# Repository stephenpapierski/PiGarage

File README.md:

> [!IMPORTANT]
> This never worked well and there are much better solutions out there. I would recommend taking a look at [Konnected](https://konnected.io/collections/shop-now?filter.p.tag=Smart+Garage+Door+Openers) Garage Door Openers, which support Hubitat, Home Assistant, Control4 and other cloud based home automation platforms.
# PiGarage
This project contains the Raspberry Pi and Hubitat driver code for a Raspberry Pi hat for controlling a garage door through Hubitat. The hardware includes a relay for actuating the garage door controller, 2 door sensor inputs (open/closed), and status LEDs to communicate door status.

See the [project wiki](https://github.com/stephenpapierski/PiGarage/wiki) to get started.

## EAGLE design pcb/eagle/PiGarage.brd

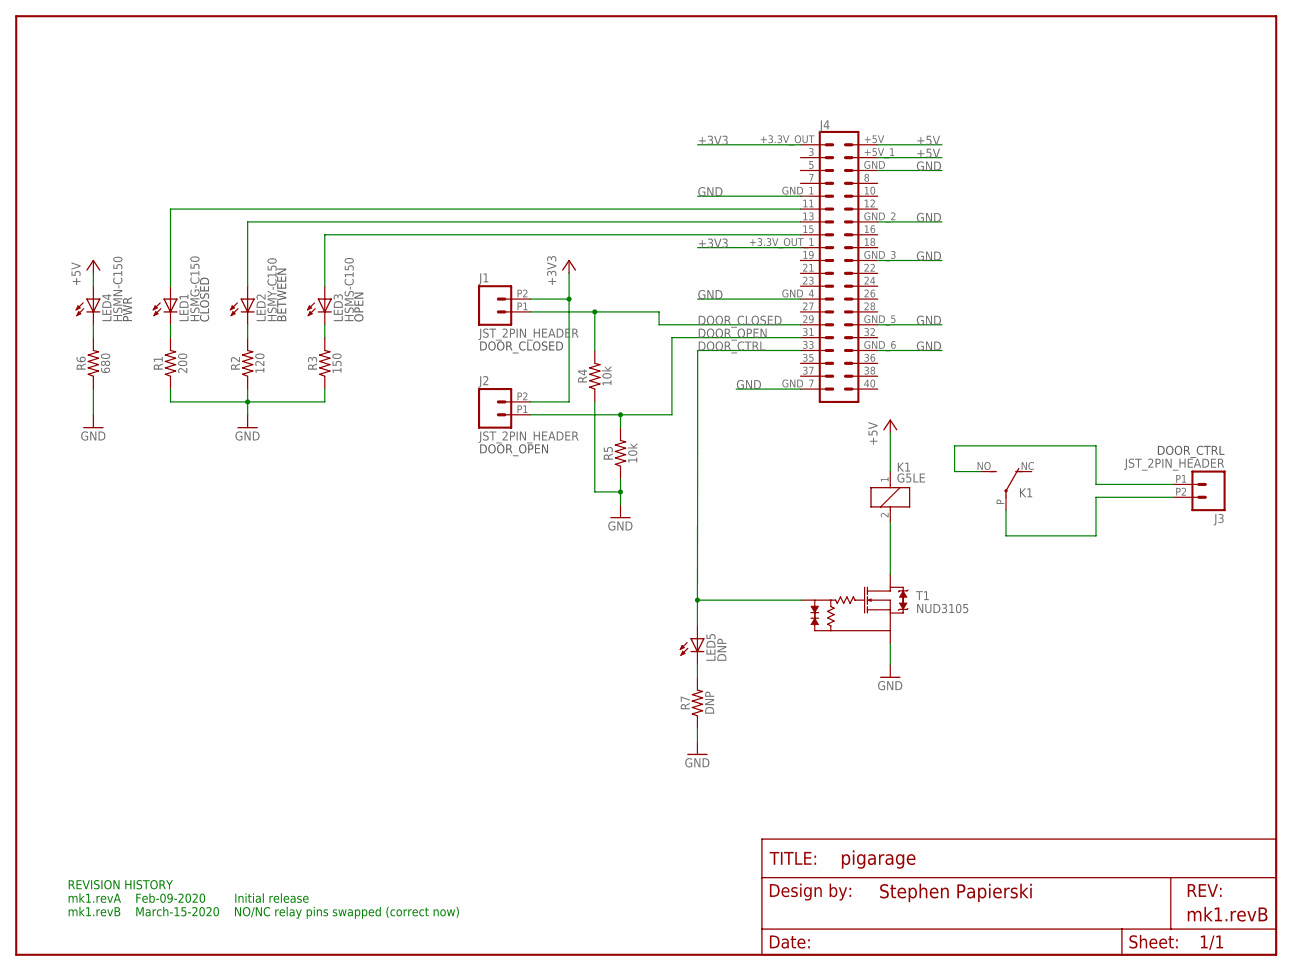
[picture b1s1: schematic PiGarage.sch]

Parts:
FRAME1: FRAME-LETTERNO_PACKAGE; DUMMY
J1, J2, J3: JST_2PIN_HEADER; JST_2PIN_RIGHT_HEADER
J4: RPI-GPIO-20X2
K1: G5LE
LED1: HSMG-C150; CHIPLED_1206
LED2: HSMY-C150; CHIPLED_1206
LED3: HSMS-C150; CHIPLED_1206
LED4: HSMN-C150; CHIPLED_1206
LED5: DNP; CHIPLED_1206
R1: 200; 0805
R2: 120; 0805
R3: 150; 0805
R4, R5: 10k; 0805
R6: 680; 0805
R7: DNP; 0805
T1: NUD3105; SOT23

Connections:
+3V3: J1.P2 (2), J2.P2 (2), J4.+3.3V_OUT (1), J4.+3.3V_OUT_1 (17)
+5V: J4.+5V (2), J4.+5V_1 (4), K1.1, LED4.A
DOOR_CLOSED: J1.P1 (1), J4.29, R4.2
DOOR_CTRL: J4.33, LED5.A, T1.1 (G)
DOOR_OPEN: J2.P1 (1), J4.31, R5.2
GND: J4.GND (6), J4.GND_1 (9), J4.GND_2 (14), J4.GND_3 (20), J4.GND_4 (25), J4.GND_5 (30), J4.GND_6 (34), J4.GND_7 (39), R1.1, R2.1, R3.1, R4.1, R5.1, R6.1, R7.1, T1.2 (S)
unnamed: K1.2, T1.3 (D)
unnamed: LED5.C, R7.2
unnamed: J3.P1 (1), K1.NO
unnamed: J3.P2 (2), K1.P
unnamed: LED4.C, R6.2
unnamed: J4.11, LED1.A
unnamed: J4.13, LED2.A
unnamed: J4.15, LED3.A
unnamed: LED1.C, R1.2
unnamed: LED2.C, R2.2
unnamed: LED3.C, R3.2

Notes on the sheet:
CLOSED
BETWEEN
OPEN
PWR
DOOR_CLOSED
DOOR_OPEN
DOOR_CTRL
REVISION HISTORY mk1.revA Feb-09-2020 Initial release mk1.revB March-15-2020 NO/NC relay pins swapped (correct now)

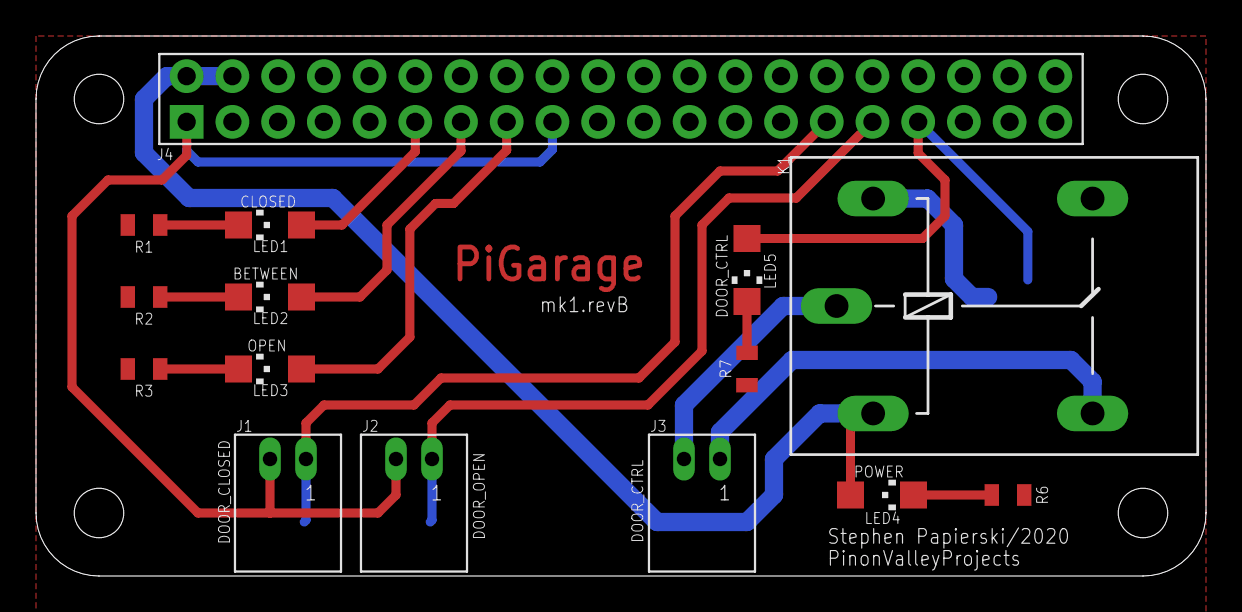
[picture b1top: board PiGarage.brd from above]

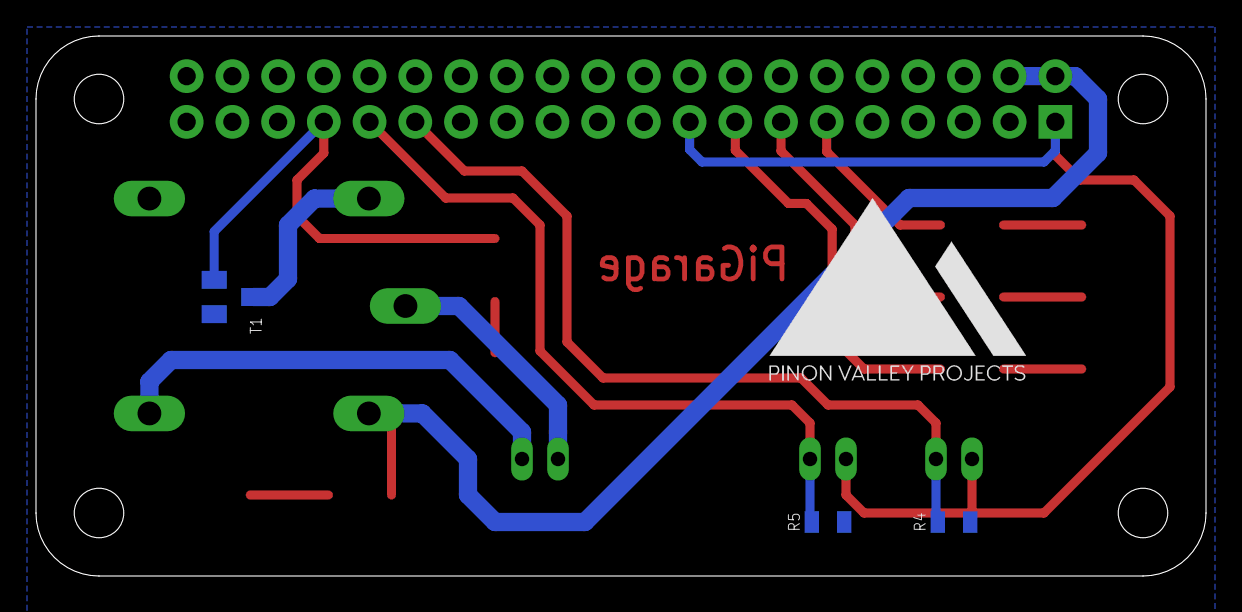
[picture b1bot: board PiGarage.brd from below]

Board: 2 copper layers, 65.0 x 30.0 mm, 19 parts (3 on the bottom side), 17 nets.

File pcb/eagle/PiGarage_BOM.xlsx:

Description | Manufacturer | Part # | Device | Package | Value | Reference Designator | Vendor | Unit Cost | Quantity | Extended Cost | Shipping | Total | Link
2x20 Header | Pololu | 1037.0 | RPI-GPIO-20x2 |  |  | J4 | Pololu | 1.25 | 1.0 | 1.25 |  | 1.25 | https://www.pololu.com/product/1037
M2.5 Standoffs (4-pack) | Pololu | 1952.0 |  |  |  |  | Pololu | 1.39 | 1.0 | 1.39 |  | 1.39 | https://www.pololu.com/product/1952
M2.5 Screws (25-pack) | Pololu | 1968.0 |  |  |  |  | Pololu | 0.99 | 1.0 | 0.99 |  | 0.99 | https://www.pololu.com/product/1968
M2.5 Nuts (25-pack) | Pololu | 1967.0 |  |  |  |  | Pololu | 0.99 | 1.0 | 0.99 |  | 0.99 | https://www.pololu.com/product/1967
 |  |  |  |  |  |  |  |  |  |  | 4.95 | 9.57
Relay | Omron | G5LE-1A4 DC5 | G5LE |  |  | K1 | Digi-Key | 1.41 | 1.0 | 1.41 |  | 1.41 | https://www.digikey.com/product-detail/en/omron-electronics-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
Relay Driver | ON Semiconductor | NUD3105LT1G | NUD3105 | SOT23 |  | T1 | Digi-Key | 0.44 | 1.0 | 0.44 |  | 0.44 | https://www.digikey.com/product-detail/en/on-semiconductor/N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
120 Ohm LED Resistor | Yageo | AC0805FR-07120RL | RESISTOR_0805 | 0805 | 120 | R2 | Digi-Key | 0.1 | 1.0 | 0.1 |  | 0.1 | https://www.digikey.com/product-detail/en/yageo/AC0805FR-071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
150 Ohm LED Resistor | Yageo | AC0805FR-07150RL | RESISTOR_0805 | 0805 | 150 | R3 | Digi-Key | 0.1 | 1.0 | 0.1 |  | 0.1 | https://www.digikey.com/product-detail/en/yageo/AC0805FR-071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
200 Ohm LED Resistor | Yageo | AC0805FR-07200RL | RESISTOR_0805 | 0805 | 200 | R1 | Digi-Key | 0.1 | 1.0 | 0.1 |  | 0.1 | https://www.digikey.com/product-detail/en/yageo/AC0805FR-072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
680 Ohm LED Resistor | Yageo | AC0805JR-07680RL | RESISTOR_0805 | 0805 | 680 | R6 | Digi-Key | 0.1 | 1.0 | 0.1 |  | 0.1 | https://www.digikey.com/product-detail/en/yageo/AC0805JR-076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
10k Resistor | Yageo | AC0805FR-0710KL | RESISTOR_0805 | 0805 | 10k | R4, R5 | Digi-Key | 0.1 | 1.0 | 0.1 |  | 0.1 | https://www.digikey.com/product-detail/en/yageo/AC0805FR-071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
Door Ctrl LED Resistor |  |  |  |  | DNP | R7 |  |  |  |  |  | 0
Green Closed LED | Broadcom Limited | HSMG-C150 | CHIPLED_1206 | 1206 |  | LED1 | Digi-Key | 0.5 | 1.0 | 0.5 |  | 0.5 | https://www.digikey.com/product-detail/en/broadcom-limited/H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
Yellow In Between LED | Broadcom Limited | HSMY-C150 | CHIPLED_1206 | 1206 |  | LED2 | Digi-Key | 0.53 | 1.0 | 0.53 |  | 0.53 | https://www.digikey.com/product-detail/en/broadcom-limited/H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
Red Open LED | Broadcom Limited | HSMS-C150 | CHIPLED_1206 | 1206 |  | LED3 | Digi-Key | 0.53 | 1.0 | 0.53 |  | 0.53 | https://www.digikey.com/product-detail/en/broadcom-limited/H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
Blue PWR LED | Broadcom Limited | HSMN-C150 | CHIPLED_1206 | 1206 |  | LED4 | Digi-Key | 1.05 | 1.0 | 1.05 |  | 1.05 | https://www.digikey.com/product-detail/en/broadcom-limited/H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
Door Ctrl LED |  |  |  |  | DNP | LED5 |  |  |  |  |  | 0
Door Sensor | SparkFun Electronics | COM-13247 |  |  |  |  | Digi-Key | 3.5 | 2.0 | 7 |  | 7 | https://www.digikey.com/product-detail/en/sparkfun-electroni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
JST Connector and Wire Assembly | SparkFun Electronics | PRT-09914 | JST_2PIN_HEADER |  |  | J1, J2, J3 | Digi-Key | 0.95 | 3.0 | 2.85 |  | 2.85 | https://www.digikey.com/product-detail/en/sparkfun-electroni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
 |  |  |  |  |  |  |  |  |  |  | 8.99 | 23.8
Circuit Board | Osh Park | PiGarage mk1.revA |  |  |  |  |  | 16.35 | 1.0 | 15.1 |  | 15.1 | https://oshpark.com/shared_projects/nDRBJeuH
 |  |  |  |  |  |  |  |  |  |  | 0.0 | 15.1
 |  |  |  |  |  |  |  |  |  |  | Total | 48.47

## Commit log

2019-03-04 Start of distance sensor class
2020-01-20 Organizing files into hubitat drivers and raspi program
2020-01-20 Adding ability to handle POST requests from the raspberry pi side
2020-01-20 Adding hubitat driver code to set POST requests for open and close
2020-01-20 Updated metadata
2020-01-22 Renaming project to PiGarage
2020-01-22 Multithreaded raspi app to run main loop along side Flask app
2020-01-22 Added ability for raspi to send http post requests to hubitat
2020-01-22 Driver parse method can now parse incoming http post json content
2020-01-24 Added garageDoor class to handle sensor interaction and logic
2020-01-24 Hubitat driver updates current state from raspi post requests
2020-02-01 Added stopped status, relay logic based on status, and a timeout value.
2020-02-01 Implemented refresh command
2020-02-01 Implemented refresh() and updated()
2020-02-01 Added lastActivity tracking and option debug logging
2020-02-02 Added status led logic
2020-02-09 Adding pi-garage service file for systemd
2020-02-09 Fixing issue where unknown state was continuously reported
2020-02-09 Added lastEvent and responding attributes
2020-02-10 Grabbing hub ip from post messages so the hub ip is no longer hard coded
2020-02-11 Adding pcb files
2020-02-13 Adding formatted BOM and board renders
2020-03-15 Fixed relay NC/NO pin swap issue, bumped board rev to mk1.revB
2020-03-15 Increasing resolution of board renders
2020-03-15 Removed stray debug message, fixed spelling of PinonValleyProjects
2020-03-15 Correcting GarageDoorControl attribute name to door
2020-11-23 Making simpler and more reliable with single thread and interrupts

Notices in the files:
parts and their libraries:
SparkFun-Resistors: Licensing: Creative Commons ShareAlike 4.0 International - https://creativecommons.org/licenses/by-sa/4.0
